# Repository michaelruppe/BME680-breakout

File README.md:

# BME680-breakout
A simple breakout for the BME680 atmospheric sensor. JSH SH connecter (Qwiic / STEMMA QT / PiicoDev compatible)

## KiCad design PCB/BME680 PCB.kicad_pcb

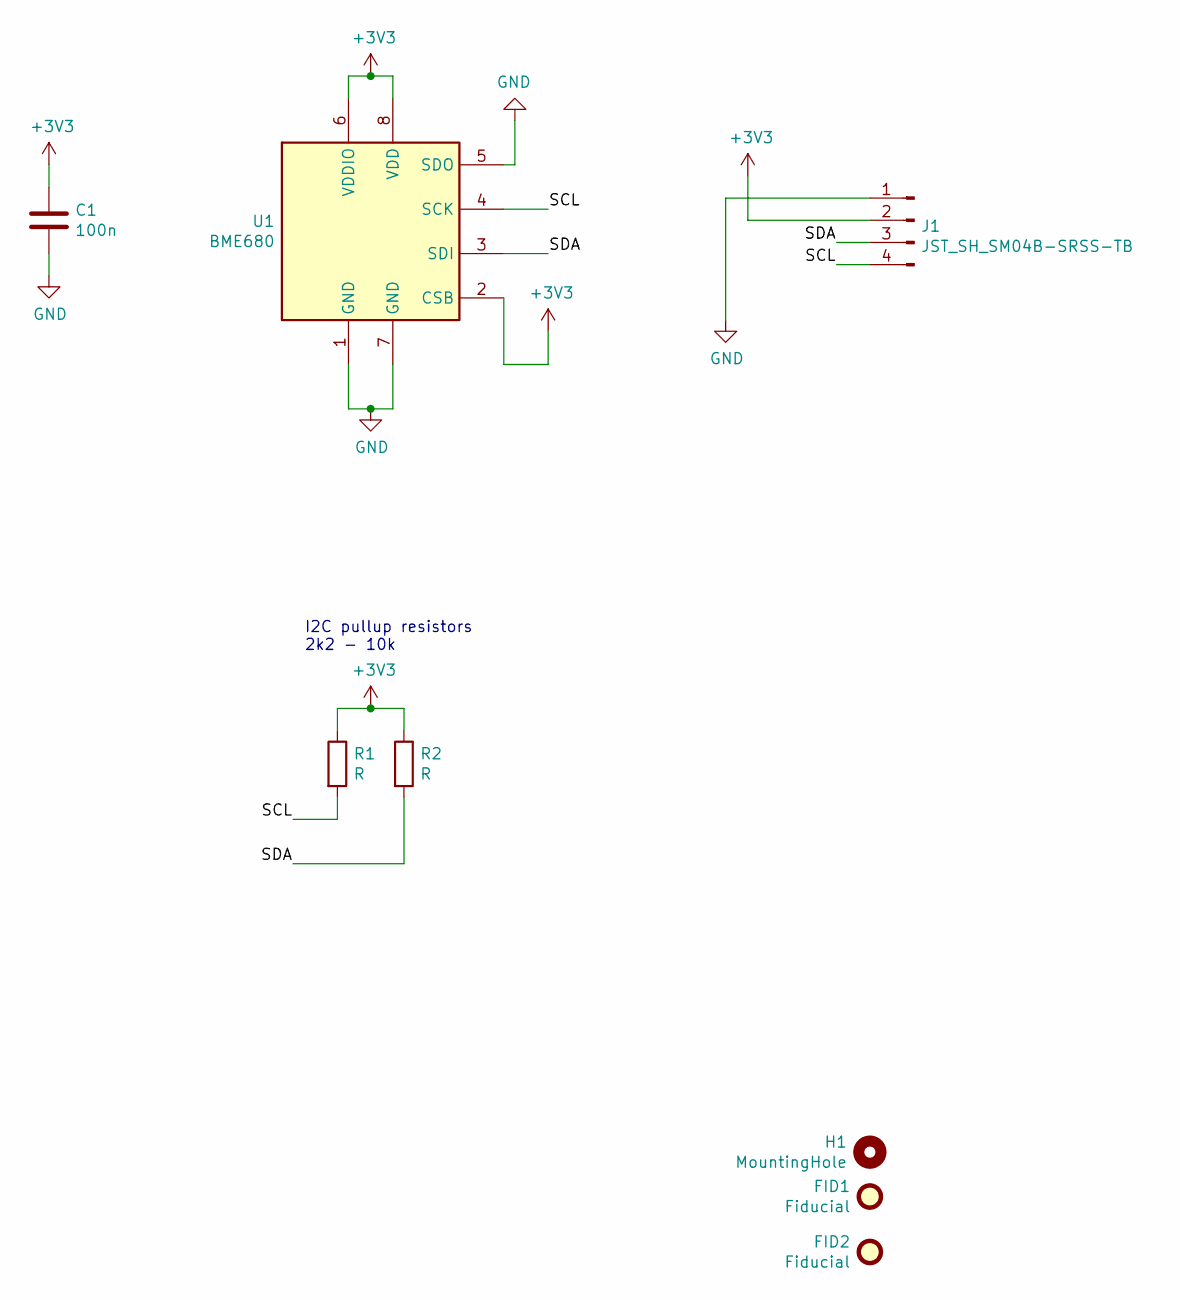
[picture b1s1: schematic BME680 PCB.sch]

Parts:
C1: 100n; C_0603_1608Metric
FID1, FID2: Fiducial; Fiducial_1mm_Mask2mm
H1: MountingHole; MountingHole_2.2mm_M2
J1: JST_SH_SM04B-SRSS-TB; JST_SH_SM04B-SRSS-TB_1x04-1MP_P1.00mm_Horizontal
R1, R2: R; R_0603_1608Metric
U1: BME680; Bosch_LGA-8_3x3mm_P0.8mm_ClockwisePinNumbering

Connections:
+3V3: C1.1, J1.2, R1.1, R2.1, U1.2 (CSB), U1.6 (VDDIO), U1.8 (VDD)
/SCL: J1.4, R1.2, U1.4 (SCK)
/SDA: J1.3, R2.2, U1.3 (SDI)
GND: C1.2, J1.1, U1.1 (GND), U1.5 (SDO), U1.7 (GND)

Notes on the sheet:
I2C pullup resistors 2k2 - 10k

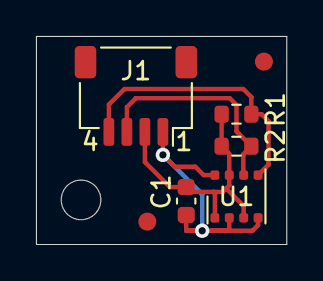
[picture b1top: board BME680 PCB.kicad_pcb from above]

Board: 2 copper layers, 13.9 x 11.6 mm, 8 parts (0 on the bottom side), 4 nets.
